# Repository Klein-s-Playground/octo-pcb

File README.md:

# octo-pcb
KiCAD projects for PCB design files

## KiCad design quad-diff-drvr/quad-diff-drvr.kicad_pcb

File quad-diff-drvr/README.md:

# quad-diff-driver

 - is a Pi HAT that can stack 4x to a Pi
 - total of 16 strips to a Pi with this cool [parallel driver](https://iosoft.blog/2020/09/29/raspberry-pi-multi-channel-ws2812/) code
 - Drive 4x 150 LED strips up to 9A per channel out
 - Uses quad differential RS-485 driver for 1m+ runs of twisted pair data line
 - Control power out to each strip individually
 - Power monitoring of VA , VB, Pi 5V in/out with interrupt signals
 - max 30A all channels per HAT, 15A per VA / VB on a HAT
 - Should cost around $16 in parts ([BoM](https://docs.google.com/spreadsheets/d/1N1vn6LuwAwEPZ860a-0pwzuY52BjjF7snLwd1W7JV2M/edit?usp=sharing)) + $2.5 per PCB ([DirtyPCB](https://dirtypcbs.com/store/pcbs/about)) at quantity

## MacroFab Quote

See Turnkey PCB Quote from [MacroFab](https://factory.macrofab.com/pcb/g5n1ef7/1/design)
 - 10 PCBAs
 - $1k total for $100 / ea.
 - Est. ship date Mar. 8

## Design Files

| Schematic ([PDF](img/quad-diff-drvr.pdf)) | PCB Layout |
:-------------------------:|:-------------------------:
 |

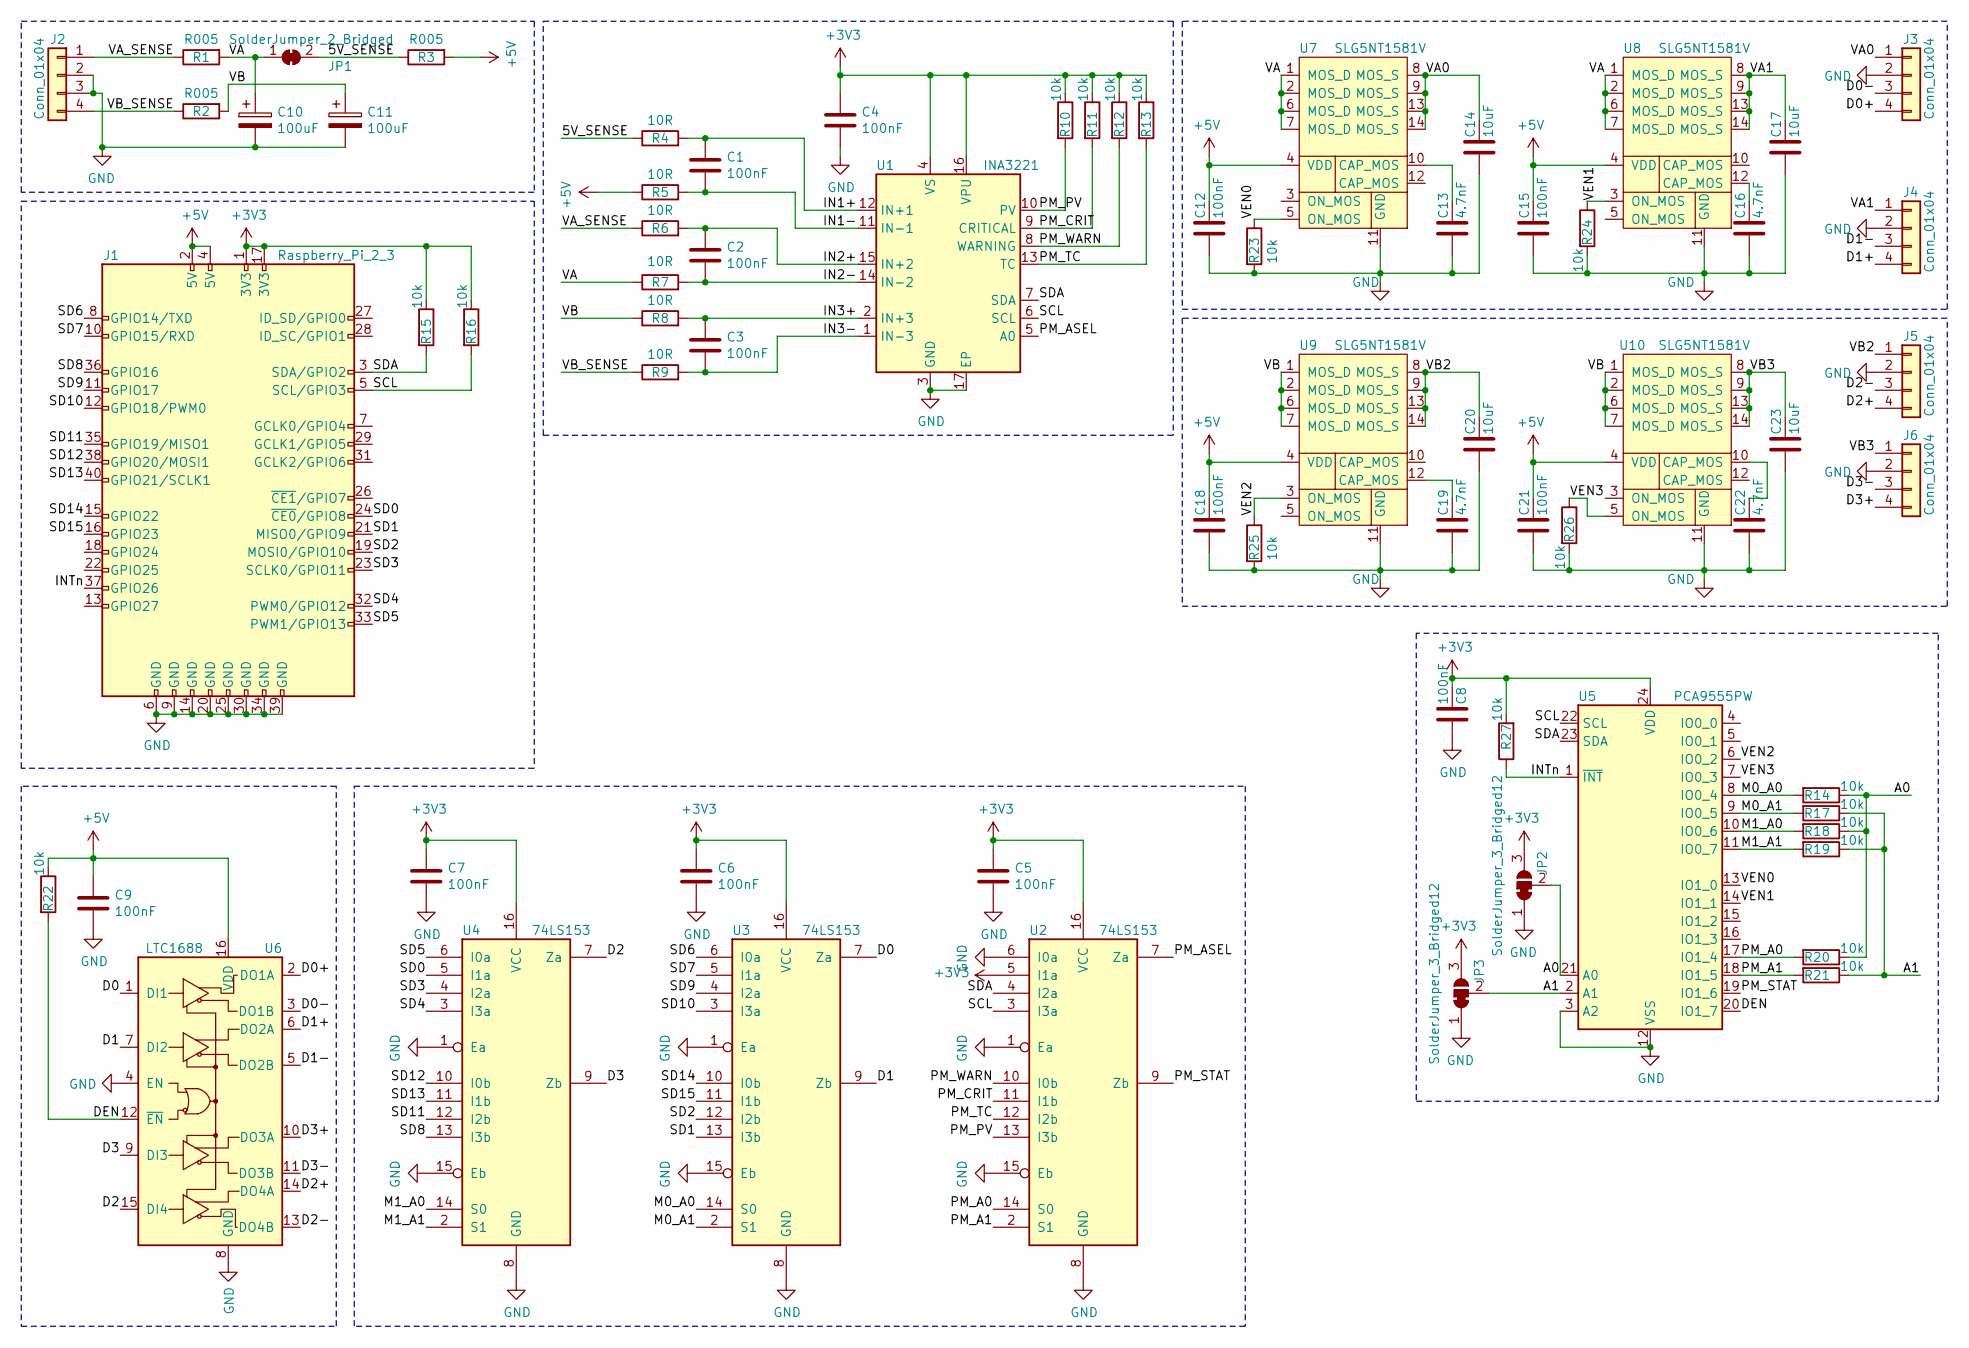
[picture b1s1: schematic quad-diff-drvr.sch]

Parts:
C1, C2, C3, C4, C5, C6, C7, C8, C9, C12, C15, C18, C21: 100nF; C_0603_1608Metric
C10, C11: 100uF; CP_Elec_6.3x7.7
C13, C16, C19, C22: 4.7nF; C_0603_1608Metric
C14, C17, C20, C23: 10uF; C_1206_3216Metric
J1: Raspberry_Pi_2_3; PinHeader_2x20_P2.54mm_Vertical
J2, J3, J4, J5, J6: Conn_01x04; PhoenixContact_MSTBA_2,5_4-G_1x04_P5.00mm_Horizontal
JP1: SolderJumper_2_Bridged; SolderJumper-2_P1.3mm_Bridged2Bar_RoundedPad1.0x1.5mm
JP2, JP3: SolderJumper_3_Bridged12; SolderJumper-3_P1.3mm_Bridged2Bar12_RoundedPad1.0x1.5mm
R1, R2, R3: R005; R_1206_3216Metric
R4, R5, R6, R7, R8, R9: 10R; R_0603_1608Metric
R10, R11, R12, R13, R14, R15, R16, R17, R18, R19, R20, R21, R22, R23, R24, R25, R26, R27: 10k; R_0603_1608Metric
U1: INA3221; Texas_RGV_S-PVQFN-N16_EP2.1x2.1mm
U2, U3, U4: 74LS153; TSSOP-16_4.4x5mm_P0.65mm
U5: PCA9555PW; TSSOP-24_4.4x7.8mm_P0.65mm
U6: LTC1688; SOIC-16_3.9x9.9mm_P1.27mm
U7, U8, U9, U10: SLG5NT1581V; QFN-28_1x3_Pitch0.4mm

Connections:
+3V3: C4.1, C5.1, C6.1, C7.1, C8.1, J1.1 (3V3), J1.17 (3V3), JP2.3 (B), JP3.3 (B), R10.1, R11.1, R12.1, R13.1, R15.1, R16.1, R27.2, U1.4 (VS), U1.16 (VPU), U2.5 (I1a), U2.16 (VCC), U3.16 (VCC), U4.16 (VCC), U5.24 (VDD)
+5V: C9.1, C12.1, C15.1, C18.1, C21.1, J1.2 (5V), J1.4 (5V), R3.2, R5.1, R22.1, U6.16 (VDD), U7.4 (VDD), U8.4 (VDD), U9.4 (VDD), U10.4 (VDD)
/5V_SENSE: JP1.2 (B), R3.1, R4.1
/A0: JP2.2 (C), R14.1, R18.1, R20.1, U5.21 (A0)
/A1: JP3.2 (C), R17.1, R19.1, R21.1, U5.2 (A1)
/D0: U3.7 (Za), U6.1 (DI1)
/D0+: J3.4, U6.2 (DO1A)
/D0-: J3.3, U6.3 (DO1B)
/D1: U3.9 (Zb), U6.7 (DI2)
/D1+: J4.4, U6.6 (DO2A)
/D1-: J4.3, U6.5 (DO2B)
/D2: U4.7 (Za), U6.15 (DI4)
/D2+: J5.4, U6.14 (DO4A)
/D2-: J5.3, U6.13 (DO4B)
/D3: U4.9 (Zb), U6.9 (DI3)
/D3+: J6.4, U6.10 (DO3A)
/D3-: J6.3, U6.11 (DO3B)
/DEN: R22.2, U5.20 (IO1_7), U6.12 (~EN)
/IN1+: C1.1, R4.2, U1.12 (IN+1)
/IN1-: C1.2, R5.2, U1.11 (IN-1)
/IN2+: C2.1, R6.2, U1.15 (IN+2)
/IN2-: C2.2, R7.2, U1.14 (IN-2)
/IN3+: C3.1, R8.2, U1.2 (IN+3)
/IN3-: C3.2, R9.2, U1.1 (IN-3)
/INTn: J1.37 (GPIO26), R27.1, U5.1 (~INT)
/M0_A0: R14.2, U3.14 (S0), U5.8 (IO0_4)
/M0_A1: R17.2, U3.2 (S1), U5.9 (IO0_5)
/M1_A0: R18.2, U4.14 (S0), U5.10 (IO0_6)
/M1_A1: R19.2, U4.2 (S1), U5.11 (IO0_7)
/PM_A0: R20.2, U2.14 (S0), U5.17 (IO1_4)
/PM_A1: R21.2, U2.2 (S1), U5.18 (IO1_5)
/PM_ASEL: U1.5 (A0), U2.7 (Za)
/PM_CRIT: R11.2, U1.9 (CRITICAL), U2.11 (I1b)
/PM_PV: R10.2, U1.10 (PV), U2.13 (I3b)
/PM_STAT: U2.9 (Zb), U5.19 (IO1_6)
/PM_TC: R13.2, U1.13 (TC), U2.12 (I2b)
/PM_WARN: R12.2, U1.8 (WARNING), U2.10 (I0b)
/SCL: J1.5 (SCL/GPIO3), R16.2, U1.6 (SCL), U2.3 (I3a), U5.22 (SCL)
/SD0: J1.24 (~CE0~/GPIO8), U4.5 (I1a)
/SD1: J1.21 (MISO0/GPIO9), U3.13 (I3b)
/SD2: J1.19 (MOSI0/GPIO10), U3.12 (I2b)
/SD3: J1.23 (SCLK0/GPIO11), U4.4 (I2a)
/SD4: J1.32 (PWM0/GPIO12), U4.3 (I3a)
/SD5: J1.33 (PWM1/GPIO13), U4.6 (I0a)
/SD6: J1.8 (GPIO14/TXD), U3.6 (I0a)
/SD7: J1.10 (GPIO15/RXD), U3.5 (I1a)
/SD8: J1.36 (GPIO16), U4.13 (I3b)
/SD9: J1.11 (GPIO17), U3.4 (I2a)
/SD10: J1.12 (GPIO18/PWM0), U3.3 (I3a)
/SD11: J1.35 (GPIO19/MISO1), U4.12 (I2b)
/SD12: J1.38 (GPIO20/MOSI1), U4.10 (I0b)
/SD13: J1.40 (GPIO21/SCLK1), U4.11 (I1b)
/SD14: J1.15 (GPIO22), U3.10 (I0b)
/SD15: J1.16 (GPIO23), U3.11 (I1b)
/SDA: J1.3 (SDA/GPIO2), R15.2, U1.7 (SDA), U2.4 (I2a), U5.23 (SDA)
/VA: C10.1, JP1.1 (A), R1.2, R7.1, U7.1 (MOS_D), U7.2 (MOS_D), U7.6 (MOS_D), U7.7 (MOS_D), U8.1 (MOS_D), U8.2 (MOS_D), U8.6 (MOS_D), U8.7 (MOS_D)
/VA0: C14.1, J3.1, U7.8 (MOS_S), U7.9 (MOS_S), U7.13 (MOS_S), U7.14 (MOS_S)
/VA1: C17.1, J4.1, U8.8 (MOS_S), U8.9 (MOS_S), U8.13 (MOS_S), U8.14 (MOS_S)
/VA_SENSE: J2.1, R1.1, R6.1
/VB: C11.1, R2.2, R8.1, U9.1 (MOS_D), U9.2 (MOS_D), U9.6 (MOS_D), U9.7 (MOS_D), U10.1 (MOS_D), U10.2 (MOS_D), U10.6 (MOS_D), U10.7 (MOS_D)
/VB2: C20.1, J5.1, U9.8 (MOS_S), U9.9 (MOS_S), U9.13 (MOS_S), U9.14 (MOS_S)
/VB3: C23.1, J6.1, U10.8 (MOS_S), U10.9 (MOS_S), U10.13 (MOS_S), U10.14 (MOS_S)
/VB_SENSE: J2.4, R2.1, R9.1
/VEN0: R23.1, U5.13 (IO1_0), U7.5 (ON_MOS)
/VEN1: R24.1, U5.14 (IO1_1), U8.3 (ON_MOS)
/VEN2: R25.1, U5.6 (IO0_2), U9.3 (ON_MOS)
/VEN3: R26.1, U5.7 (IO0_3), U10.5 (ON_MOS)
GND: C4.2, C5.2, C6.2, C7.2, C8.2, C9.2, C10.2, C11.2, C12.2, C13.2, C14.2, C15.2, C16.2, C17.2, C18.2, C19.2, C20.2, C21.2, C22.2, C23.2, J1.6 (GND), J1.9 (GND), J1.14 (GND), J1.20 (GND), J1.25 (GND), J1.30 (GND), J1.34 (GND), J1.39 (GND), J2.2, J2.3, J3.2, J4.2, J5.2, J6.2, JP2.1 (A), JP3.1 (A), R23.2, R24.2, R25.2, R26.2, U1.3 (GND), U1.17 (EP), U2.1 (Ea), U2.6 (I0a), U2.8 (GND), U2.15 (Eb), U3.1 (Ea), U3.8 (GND), U3.15 (Eb), U4.1 (Ea), U4.8 (GND), U4.15 (Eb), U5.3 (A2), U5.12 (VSS), U6.4 (EN), U6.8 (GND), U7.11 (GND), U8.11 (GND), U9.11 (GND), U10.11 (GND)
unnamed: C13.1, U7.10 (CAP_MOS)
unnamed: C16.1, U8.12 (CAP_MOS)
unnamed: C19.1, U9.12 (CAP_MOS)
unnamed: C22.1, U10.10 (CAP_MOS)

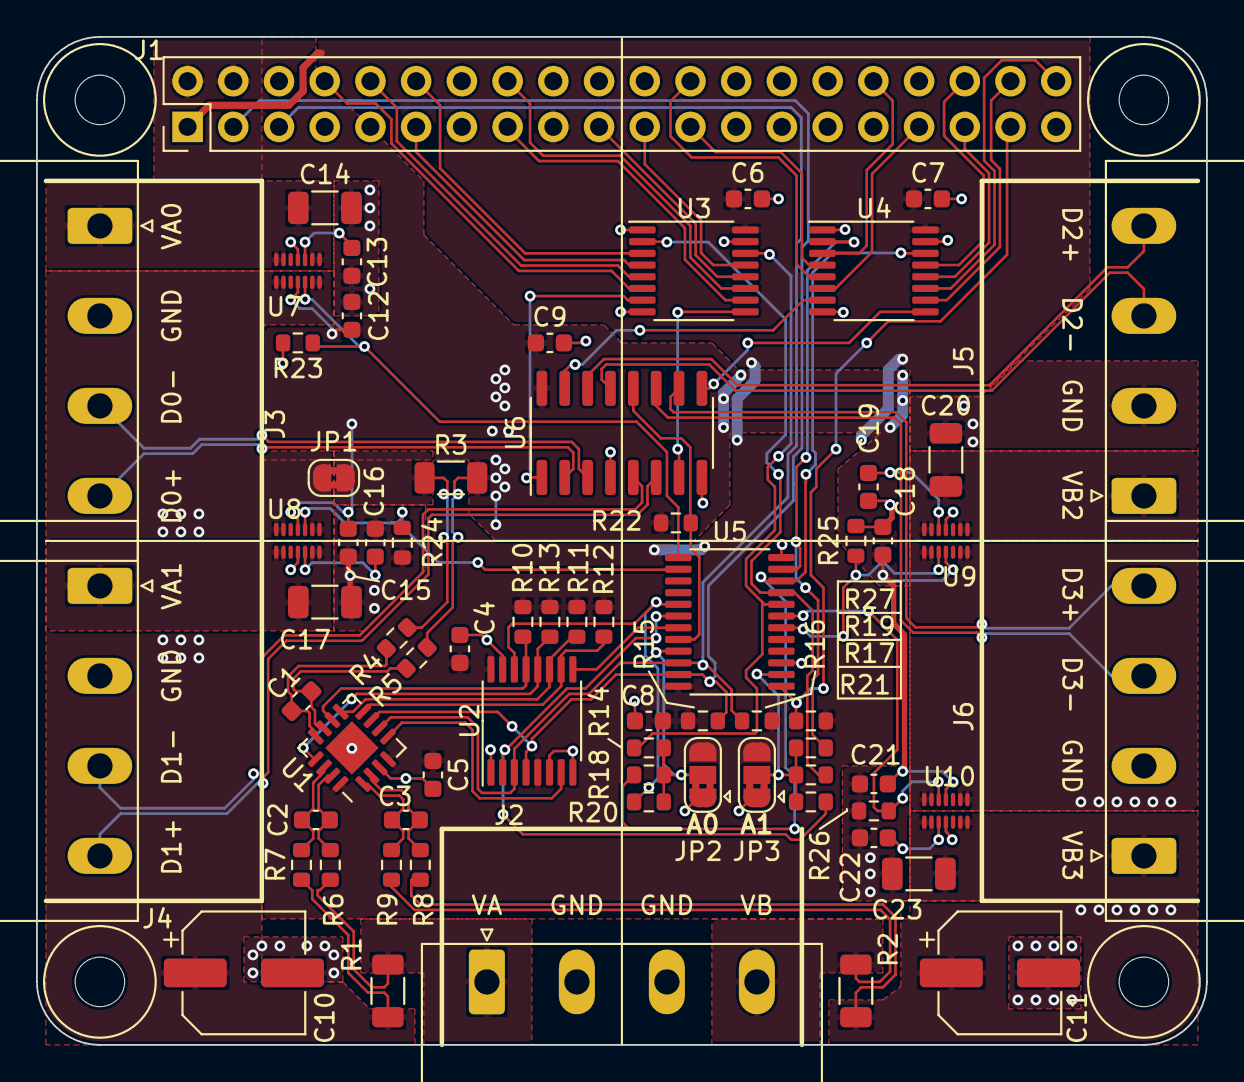
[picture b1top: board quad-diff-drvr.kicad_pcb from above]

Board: 2 copper layers, 65.0 x 56.0 mm, 69 parts (0 on the bottom side), 72 nets.

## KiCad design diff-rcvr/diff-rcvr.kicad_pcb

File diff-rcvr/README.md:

# diff-rcvr

Single unidirectional RS-485/RS-422 differential to single-ended receiver.

This 10x20mm PCB is designed to be soldered on or near a strip of WS2812B programmable LEDs to increase the range and improve noise immunity on the data line.

| Schematic | PCB Layout |
:-------------------------:|:-------------------------:
 |

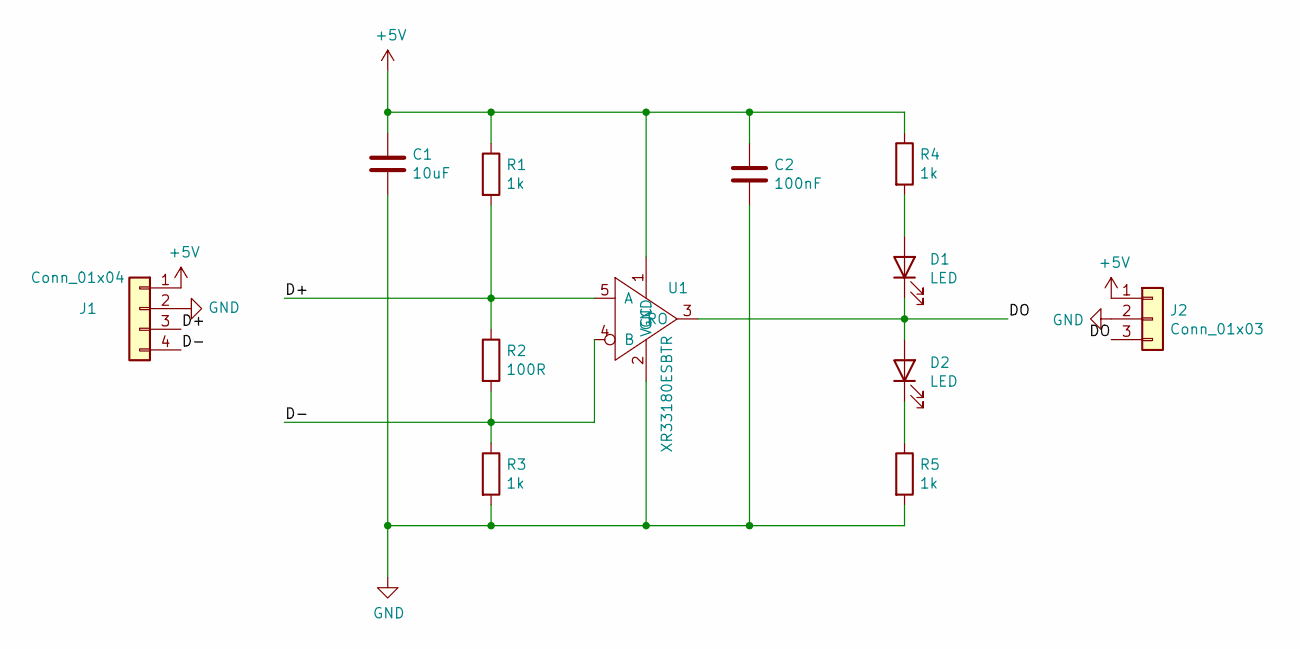
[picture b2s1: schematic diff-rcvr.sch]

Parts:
C1: 10uF; C_0805_2012Metric
C2: 100nF; C_0805_2012Metric
D1, D2: LED; LED_0805_2012Metric_Castellated
J1: Conn_01x04; PinHeader_1x04_P2.54mm_Vertical
J2: Conn_01x03; PinHeader_1x03_P2.54mm_Vertical
R1, R3, R4, R5: 1k; R_0805_2012Metric
R2: 100R; R_0805_2012Metric
U1: XR33180ESBTR; SOT-23-5

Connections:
+5V: C1.1, C2.1, J1.1, J2.1, R1.1, R4.1, U1.1 (VCC)
/D+: J1.3, R1.2, R2.1, U1.5 (A)
/D-: J1.4, R2.2, R3.1, U1.4 (B)
/DO: D1.1 (K), D2.2 (A), J2.3, U1.3 (RO)
GND: C1.2, C2.2, J1.2, J2.2, R3.2, R5.2, U1.2 (GND)
unnamed: D1.2 (A), R4.2
unnamed: D2.1 (K), R5.1

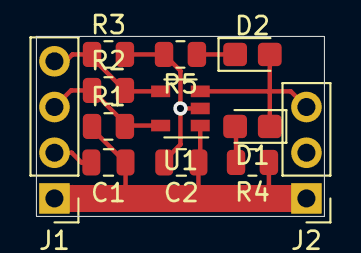
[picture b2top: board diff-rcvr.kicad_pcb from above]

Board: 2 copper layers, 16.0 x 10.0 mm, 12 parts (0 on the bottom side), 7 nets.

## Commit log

2022-01-18 diff-rcvf: first commit
2022-01-20 diff-rcvr: add README with images
2022-01-20 diff-rcvr: smaller images
2022-01-20 smaller render
2022-01-22 qdd: basic mechanical layout done
2022-01-22 qdd: power monitor added
2022-01-22 qdd: add mux0 and mux1
2022-01-22 qd: GPIO expander in
2022-01-22 qdd: driver added
2022-01-24 qdd: first pass at routing
2022-01-24 qdd: adding high-side switch
2022-01-25 qdd: unsure what got out of sync
2022-01-25 qdd: stash wip
2022-01-26 qdd: two high-side switches in
2022-01-26 qdd: VB high side switches
2022-01-27 qdd: quick and dirty route done
2022-01-28 qdd: README with pictures
2022-01-28 qdd: add macrofab quote
2022-01-29 qdd: cleaned up silkscreen
